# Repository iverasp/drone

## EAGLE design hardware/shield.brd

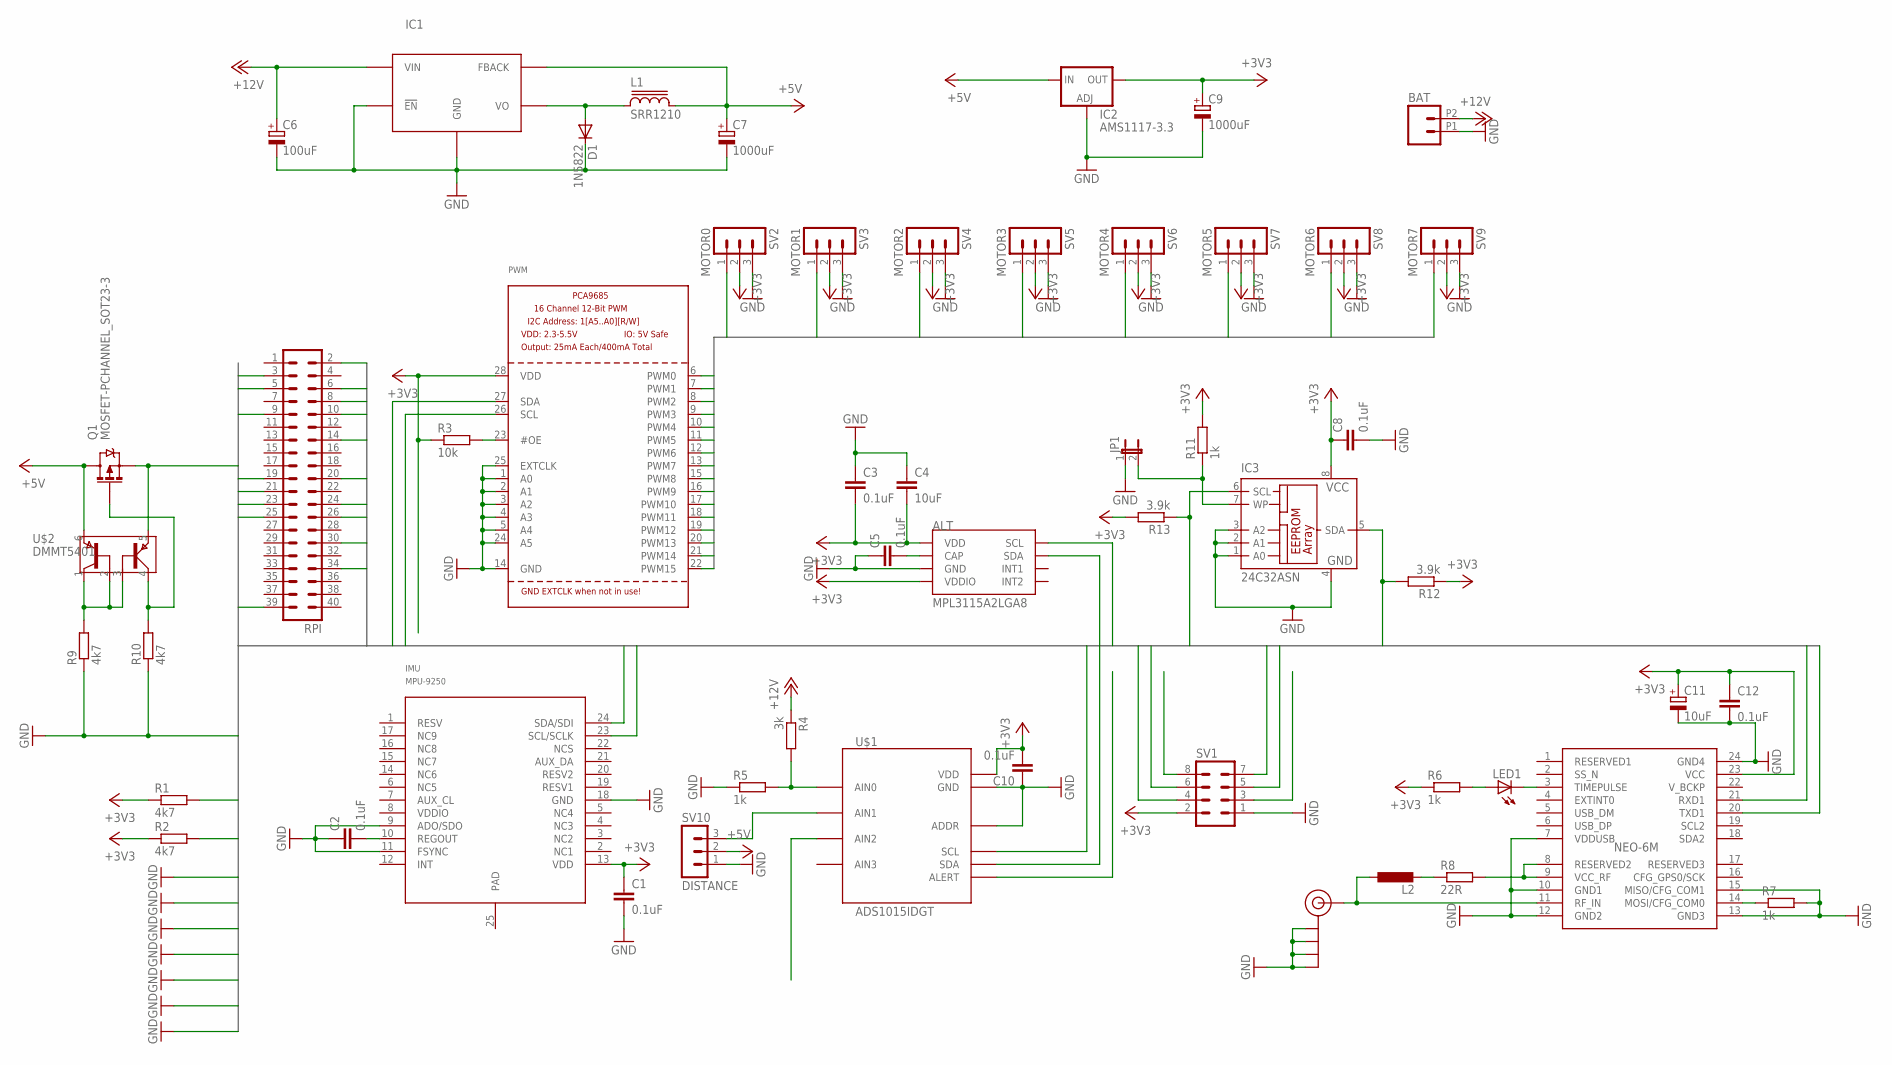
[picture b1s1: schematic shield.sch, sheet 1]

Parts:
ALT: MPL3115A2LGA8; LGA8
BAT: M022.54MM_SCREWTERM; 1X02_2.54_SCREWTERM
C1, C2, C3, C5, C8, C10, C12: 0.1uF; C1206
C4: 10uF; C1206
C6: 100uF; 153CLV-0605
C7, C9: 1000uF; 153CLV-1012
C11: 10uF; 153CLV-0405
D1: 1N5822; DO-214AC
IC1: LM2576S; TO263-5
IC2: AMS1117-3.3; SOT223
IC3: 24C32ASN; SO-08
IMU: MPU-9250; LEAD-QFN24
J$1: SMA_EDGE; SMA-EDGE
JP1: JP1E; JP1
L1: SRR1210
L2: L-EUL2012C; L2012C
LED1: LEDSMT1206; 1206
PWM: PCA9685; TSSOP28
Q1: MOSFET-PCHANNEL_SOT23-3; SOT23-3
R1, R2, R9, R10: 4k7; R1206
R3: 10k; R1206
R4: 3k; R1206
R5, R6, R7, R11: 1k; R1206
R8: 22R; R1206
R12, R13: 3.9k; R1206
RPI: MA20-2
SV1: MA04-2
SV2: MOTOR0; MA03-1
SV3: MOTOR1; MA03-1
SV4: MOTOR2; MA03-1
SV5: MOTOR3; MA03-1
SV6: MOTOR4; MA03-1
SV7: MOTOR5; MA03-1
SV8: MOTOR6; MA03-1
SV9: MOTOR7; MA03-1
SV10: DISTANCE; MA03-1
U$1: ADS1015IDGT; MSOP10_0.5
U$2: DMMT5401; SOT26
U$6: BLOX-NEO-6M; NE0-6M

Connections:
+3V3: ALT.1 (VDD), ALT.4 (VDDIO), C1.1, C3.2, C4.2, C8.1, C9.+, C10.2, C11.+, C12.1, IC2.4 (OUT), IC3.8 (VCC), IMU.13 (VDD), PWM.28 (VDD), R1.1, R2.1, R3.1, R6.1, R11.2, R12.1, R13.2, SV1.2, SV2.2, SV3.2, SV4.2, SV5.2, SV6.2, SV7.2, SV8.2, SV9.2, U$1.8 (VDD), U$6.23 (VCC)
+5V: C7.+, IC1.4 (FBACK), IC2.3 (IN), L1.2, Q1.3 (D), SV10.2, U$2.6
+12V: BAT.P2 (2), C6.+, IC1.1 (VIN), R4.1
GND: ALT.3 (GND), BAT.P1 (1), C1.2, C2.1, C3.1, C4.1, C5.1, C6.-, C7.-, C8.2, C9.-, C10.1, C11.-, C12.2, D1.C, IC1.3 (GND), IC1.5 (!EN), IC1.TAB (GND), IC2.1 (ADJ), IC3.1 (A0), IC3.2 (A1), IC3.3 (A2), IC3.4 (GND), IMU.9 (ADO/SDO), IMU.11 (FSYNC), IMU.18 (GND), J$1.GND@0 (GND), J$1.GND@1 (GND), J$1.GND@2 (GND), J$1.GND@3 (GND), JP1.1, PWM.1 (A0), PWM.2 (A1), PWM.3 (A2), PWM.4 (A3), PWM.5 (A4), PWM.14 (GND), PWM.24 (A5), PWM.25 (EXTCLK), R5.1, R7.2, R9.1, R10.1, RPI.6, RPI.9, RPI.14, RPI.20, RPI.25, RPI.30, RPI.34, RPI.39, SV1.1, SV2.3, SV3.3, SV4.3, SV5.3, SV6.3, SV7.3, SV8.3, SV9.3, SV10.1, U$1.1 (ADDR), U$1.3 (GND), U$6.7 (VDDUSB), U$6.10 (GND1), U$6.12 (GND2), U$6.13 (GND3), U$6.15 (MISO/CFG_COM1), U$6.24 (GND4)
unnamed: C2.2, IMU.10 (REGOUT)
unnamed: PWM.23 (#OE), R3.2
unnamed: ALT.2 (CAP), C5.2
unnamed: R4.2, R5.2, U$1.4 (AIN0)
unnamed: SV10.3, U$1.5 (AIN1)
unnamed: D1.A, IC1.2 (VO), L1.1
unnamed: LED1.A, R6.2
unnamed: LED1.C, U$6.3 (TIMEPULSE)
unnamed: R7.1, U$6.14 (MOSI/CFG_COM0)
unnamed: R8.2, U$6.8 (RESERVED2), U$6.9 (VCC_RF)
unnamed: L2.2, R8.1
unnamed: J$1.SIG (SIGNAL), L2.1, U$6.11 (RF_IN)
unnamed: R9.2, U$2.1, U$2.2, U$2.3
unnamed: Q1.1 (G), R10.2, U$2.4
unnamed: IC3.7 (WP), JP1.2, R11.1
PWM0: PWM.6 (PWM0), SV2.1
PWM1: PWM.7 (PWM1), SV3.1
PWM2: PWM.8 (PWM2), SV4.1
PWM3: PWM.9 (PWM3), SV5.1
PWM4: PWM.10 (PWM4), SV6.1
PWM5: PWM.11 (PWM5), SV7.1
PWM6: PWM.12 (PWM6), SV8.1
PWM7: PWM.13 (PWM7), SV9.1
PWM8: PWM.15 (PWM8)
PWM9: PWM.16 (PWM9)
PWM10: PWM.17 (PWM10)
PWM11: PWM.18 (PWM11)
PWM12: PWM.19 (PWM12)
PWM13: PWM.20 (PWM13)
PWM14: PWM.21 (PWM14)
PWM15: PWM.22 (PWM15)
RPI2: Q1.2 (S), RPI.2, U$2.5
RPI3: ALT.7 (SDA), IMU.24 (SDA/SDI), PWM.27 (SDA), R1.2, RPI.3, U$1.9 (SDA)
RPI5: ALT.8 (SCL), IMU.23 (SCL/SCLK), PWM.26 (SCL), R2.2, RPI.5, U$1.10 (SCL)
RPI8: RPI.8, U$6.21 (RXD1)
RPI10: RPI.10, U$6.20 (TXD1)
RPI19: RPI.19, SV1.6
RPI21: RPI.21, SV1.7
RPI23: RPI.23, SV1.5
RPI24: RPI.24, SV1.4
RPI26: RPI.26
RPI27: IC3.5 (SDA), R12.2
RPI28: IC3.6 (SCL), R13.1

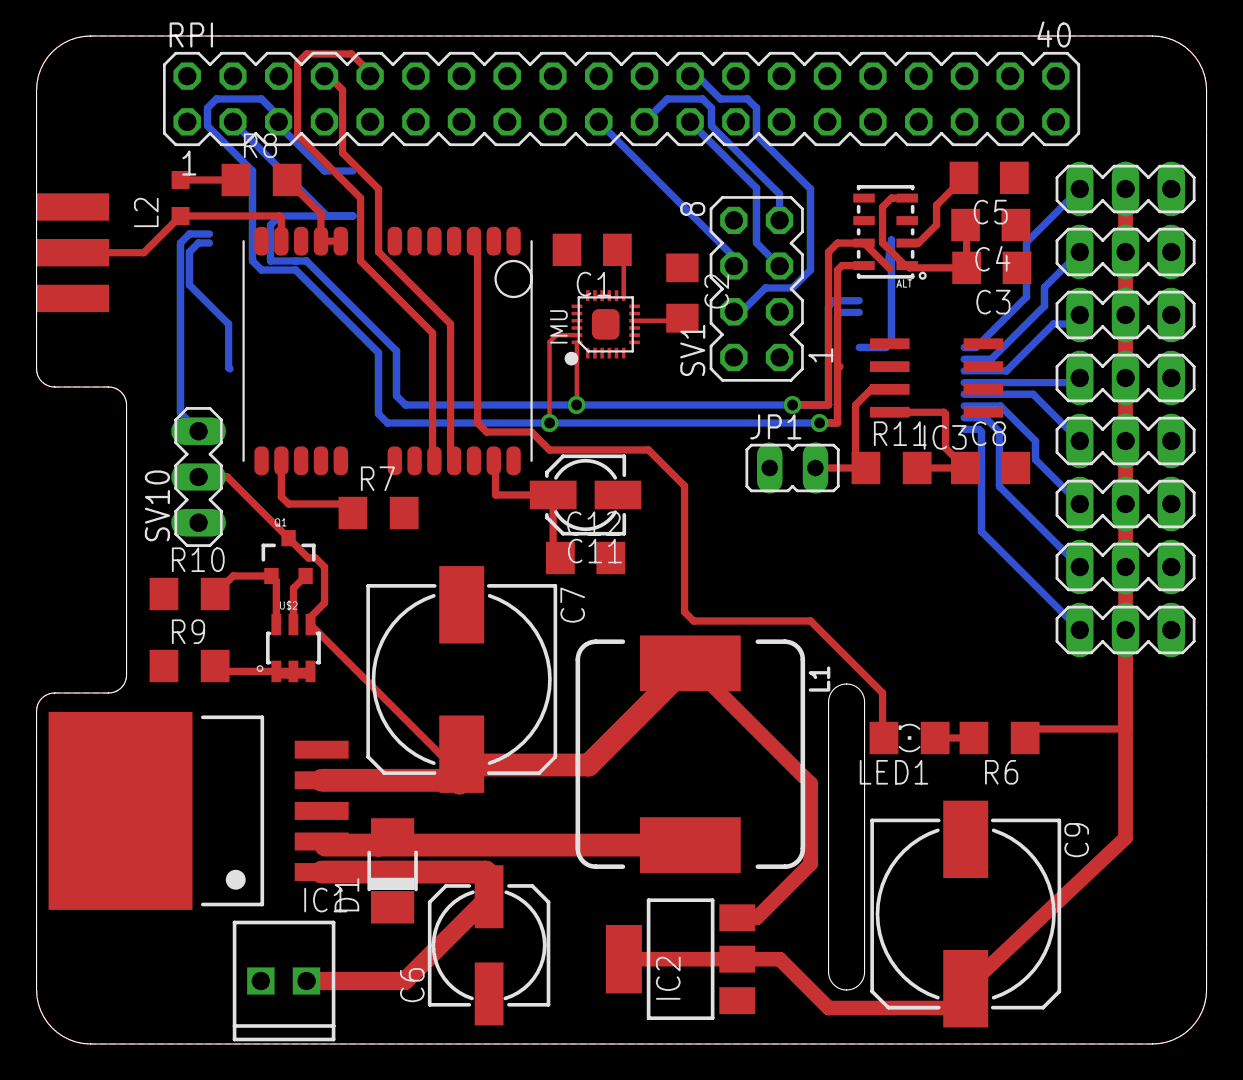
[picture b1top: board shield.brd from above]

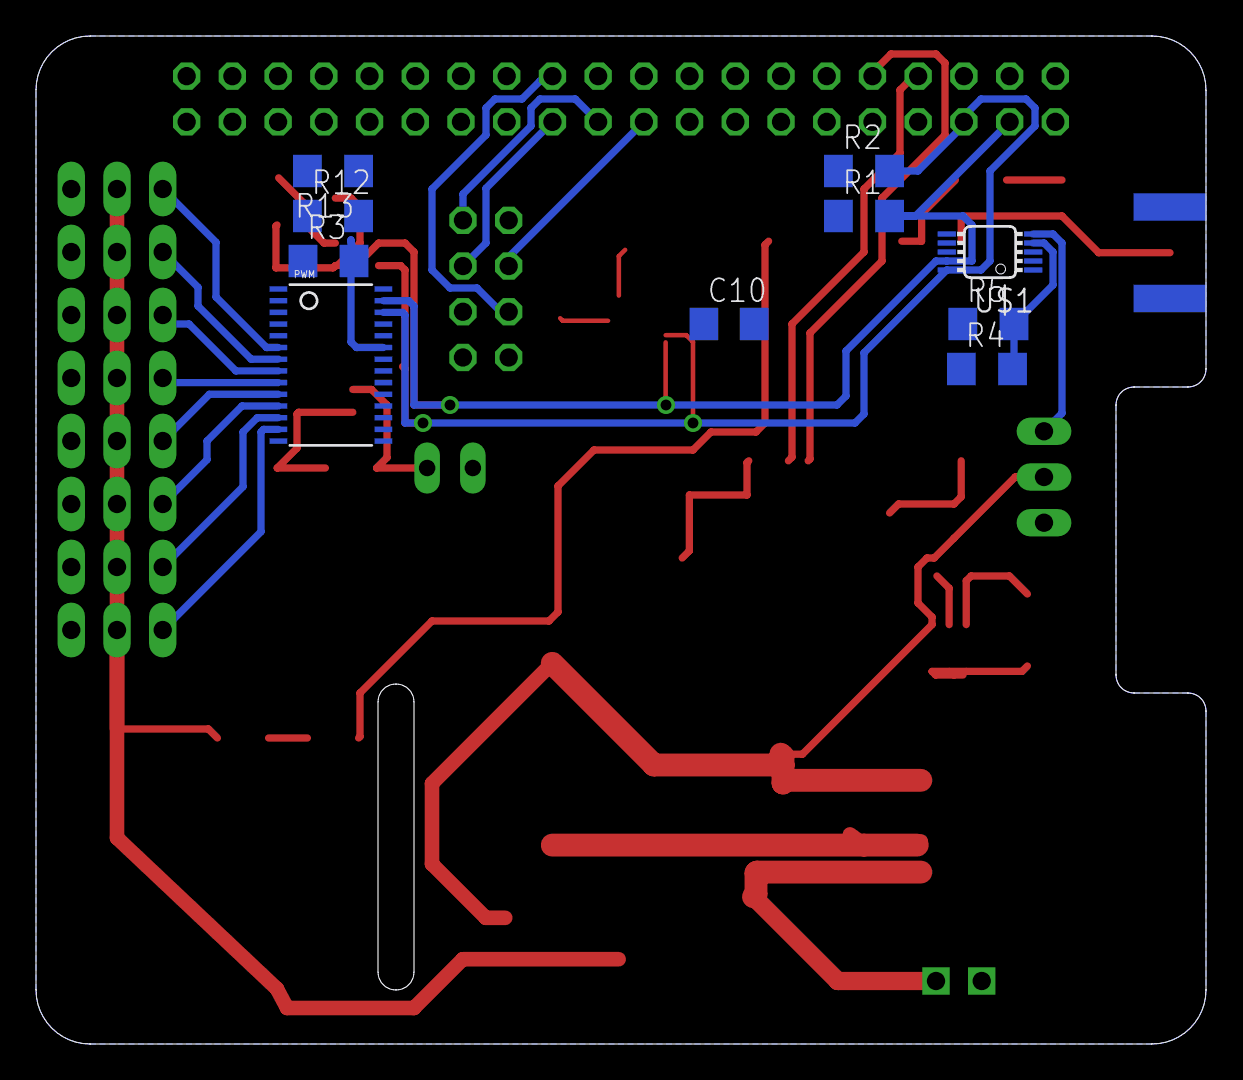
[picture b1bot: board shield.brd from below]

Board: 2 copper layers, 65.0 x 56.0 mm, 53 parts (10 on the bottom side), 38 nets.

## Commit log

2016-11-30 added gitignore
2016-11-30 added boilerplate pilot
2016-12-03 added code for invensense dmp
2016-12-10 added readme on pilot
2016-12-10 added readme on stream
2016-12-10 fixed typo
2016-12-10 added gitignore for eagle
2016-12-10 added hardware
2017-02-24 mroe drones

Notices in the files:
parts and their libraries:
SparkFun-Sensors: Licensing: Creative Commons ShareAlike 4.0 International - https://creativecommons.org/licenses/by-sa/4.0
inductor-bourns: Copyright (C) 2008, Bob Starr
